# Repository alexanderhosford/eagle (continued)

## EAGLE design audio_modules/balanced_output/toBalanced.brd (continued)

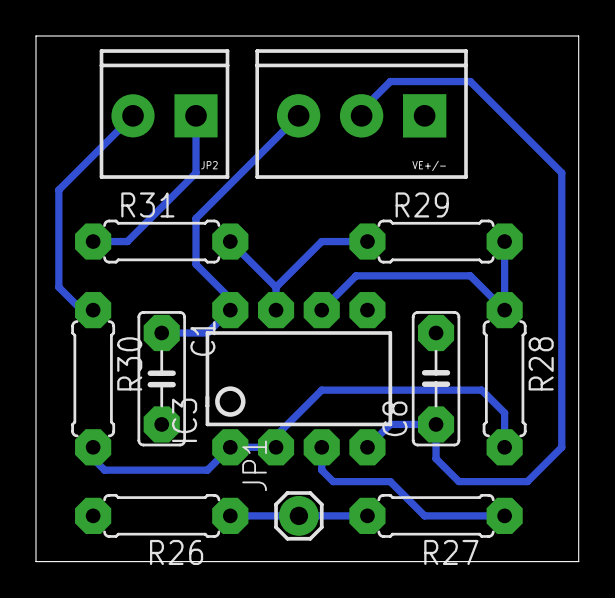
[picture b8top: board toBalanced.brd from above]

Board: 2 copper layers, 30.1 x 29.2 mm, 12 parts (0 on the bottom side), 10 nets.

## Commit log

2013-12-05 adding eagle projects
2013-12-05 reducing drill hole size on alice mic boards
2013-12-05 removing ground plane from alice mic, adding extra caps
2013-12-05 changing 100k angle to 0°
2013-12-05 backup brd file
2013-12-05 placing extra caps, smashing values and setting vector font, size, ratio
2013-12-05 routed, no DRC
2013-12-05 processed hackvana cam job
2013-12-06 Moving components, matching grid positions
2014-01-28 Restructuring project hierarchy, moving alice mic out into separate repo
2014-02-02 Moved Toby's little bits out into new repo
